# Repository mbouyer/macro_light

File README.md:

# macro_light
éclairage pour macro-photo sous-marine. Voir le wiki pour les details

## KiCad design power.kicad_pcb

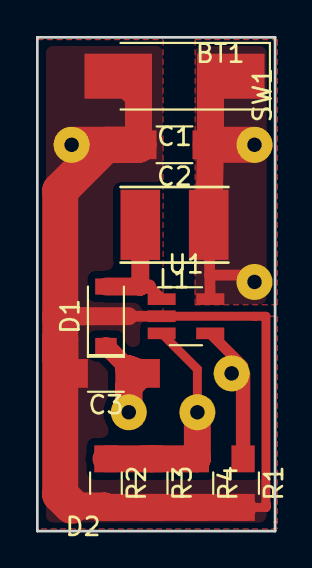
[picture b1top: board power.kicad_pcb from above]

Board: 2 copper layers, 13.2 x 27.4 mm, 13 parts (0 on the bottom side), 6 nets.

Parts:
BT1: Battery 3V; SolderWirePad_2x_0-8mmDrill
C1: 47µF 10V; CP_Tantalum_Case-U_EIA-6032-15_Hand
C2: 10µF 35V; C_1206_HandSoldering
C3: 6,8µF 50V; C_1206_HandSoldering
D1: PMEG4005EGWX; D_SOD-123
D2: LED x 6; SolderWirePad_2x_0-8mmDrill
L1: 10µ; Inductor_Taiyo-Yuden_NR-40xx_HandSoldering
R1: 100K; R_0805_HandSoldering
R2: 30; R_0805_HandSoldering
R3, R4: 15; R_0805_HandSoldering
SW1: SW_Reed; WireConnection_0.80mmDrill
U1: MCP1662; SOT-23-5_HandSoldering

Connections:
unnamed: BT1.1, C1.1, C2.1, L1.1, SW1.1, U1.5
unnamed: BT1.2, C1.2, C2.2, C3.2, R1.2, R2.2, R3.2, R4.2, U1.2
unnamed: C3.1, D1.1, D2.2
unnamed: D1.2, L1.2, U1.1
unnamed: D2.1, R2.1, R3.1, R4.1, U1.3
unnamed: R1.1, SW1.2, U1.4

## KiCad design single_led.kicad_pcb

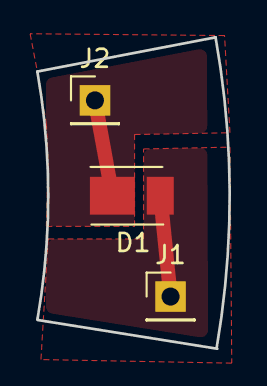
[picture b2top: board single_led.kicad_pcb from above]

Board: 2 copper layers, 10.7 x 17.3 mm, 3 parts (0 on the bottom side), 2 nets.

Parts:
D1: JE2835AWT; LED_PLCC_2835_Handsoldering
J1, J2: Conn_01x01; Pin_Header_Straight_1x01_Pitch2.54mm

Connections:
unnamed: D1.1, J2.1
unnamed: D1.2, J1.1

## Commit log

2019-01-13 Fichiers de realisations (kicad pour l'électronique et openscad pour l'impression 3D)
2019-01-13 export schema régulation en PDF
2019-01-13 Images pour le wiki
2019-01-13 Unused files.
